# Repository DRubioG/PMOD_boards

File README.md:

# PMOD_boards
 This repository include all pmods created with KiCad

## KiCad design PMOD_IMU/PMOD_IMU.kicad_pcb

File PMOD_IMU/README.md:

# PMOD_boards
 This repository include all pmods created with KiCad

## Schematic

[schematic](/salida_esquematico.pdf)

## images

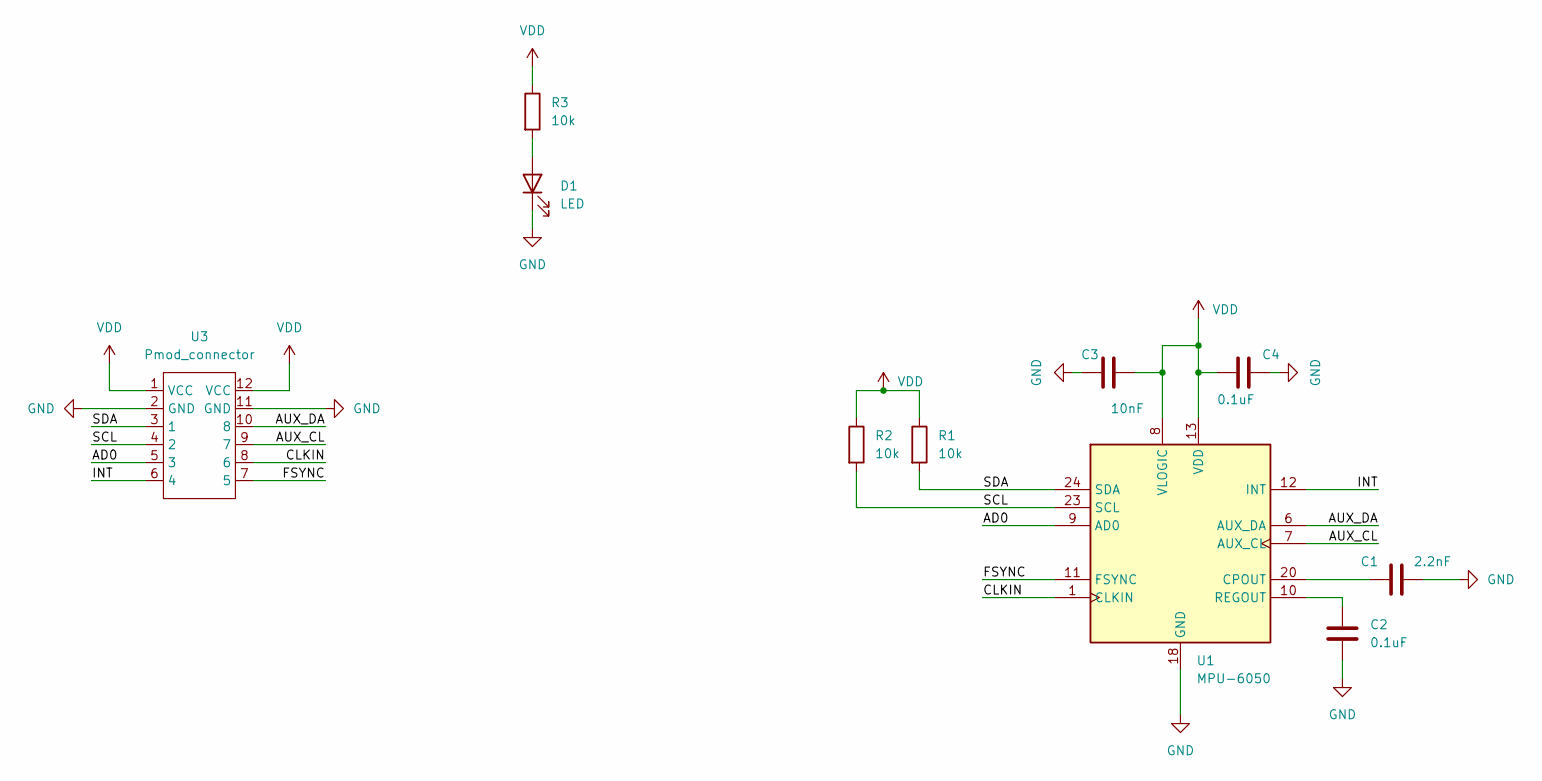
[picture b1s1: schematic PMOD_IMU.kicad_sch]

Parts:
C1: 2.2nF; C_0805_2012Metric_Pad1.18x1.45mm_HandSolder
C2, C4: 0.1uF; C_0805_2012Metric_Pad1.18x1.45mm_HandSolder
C3: 10nF; C_0805_2012Metric_Pad1.18x1.45mm_HandSolder
D1: LED; LED_0805_2012Metric_Pad1.15x1.40mm_HandSolder
R1, R2, R3: 10k; R_0805_2012Metric_Pad1.20x1.40mm_HandSolder
U1: MPU-6050; InvenSense_QFN-24_4x4mm_P0.5mm
U3: Pmod_connector; PMOD_EXTENSION_BOARD

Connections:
/AD0: U1.9 (AD0), U3.5 (3)
/AUX_CL: U1.7 (AUX_CL), U3.9 (7)
/AUX_DA: U1.6 (AUX_DA), U3.10 (8)
/CLKIN: U1.1 (CLKIN), U3.8 (6)
/FSYNC: U1.11 (FSYNC), U3.7 (5)
/INT: U1.12 (INT), U3.6 (4)
/SCL: R2.2, U1.23 (SCL), U3.4 (2)
/SDA: R1.2, U1.24 (SDA), U3.3 (1)
GND: C1.2, C2.1, C3.2, C4.2, D1.1 (K), U1.18 (GND), U3.2 (GND), U3.11 (GND)
unnamed: D1.2 (A), R3.2
unnamed: C1.1, U1.20 (CPOUT)
unnamed: C2.2, U1.10 (REGOUT)
VDD: C3.1, C4.1, R1.1, R2.1, R3.1, U1.8 (VLOGIC), U1.13 (VDD), U3.1 (VCC), U3.12 (VCC)

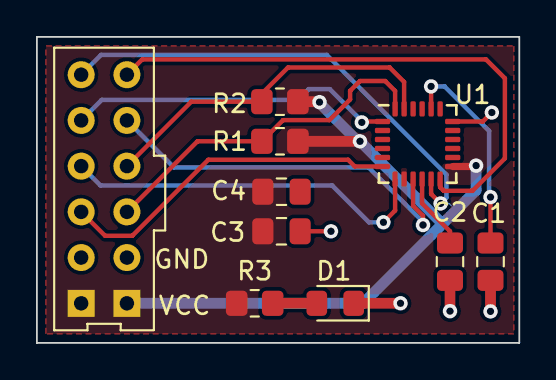
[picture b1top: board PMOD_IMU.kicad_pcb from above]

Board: 2 copper layers, 26.8 x 17.0 mm, 10 parts (0 on the bottom side), 13 nets.

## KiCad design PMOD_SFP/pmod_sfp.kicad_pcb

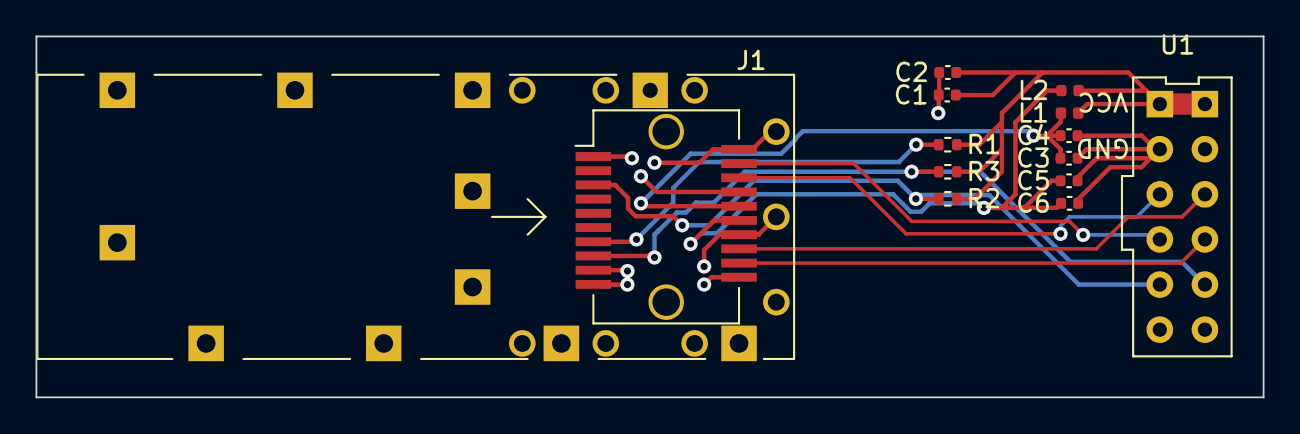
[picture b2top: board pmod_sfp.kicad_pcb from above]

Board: 2 copper layers, 69.1 x 20.3 mm, 13 parts (0 on the bottom side), 11 nets.

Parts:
C1: 22uF; C_0402_1005Metric
C2, C4, C6: 0.1uF; C_0402_1005Metric
C3, C5: 10uF; C_0402_1005Metric
J1: SFP; Connector_SFP_and_Cage
L1, L2: 220@100MHz; L_0402_1005Metric
R1, R2, R3: 4.7k; R_0402_1005Metric
U1: Pmod_connector; PMOD_EXTENSION_BOARD

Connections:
+3V3: C1.1, C2.1, L1.1, L2.1, R1.1, R2.1, R3.2, U1.1 (VCC), U1.12 (VCC)
/SFP_LOSS: J1.8 (RX_LOS), R3.1, U1.8 (6)
/SFP_RX_N: J1.12 (RD-), U1.9 (7)
/SFP_RX_P: J1.13 (RD+), U1.10 (8)
/SFP_TX_DIS: J1.3 (TX_DISABLE), R2.2, U1.5 (3)
/SFP_TX_N: J1.19 (TD-), U1.4 (2)
/SFP_TX_P: J1.18 (TD+), U1.3 (1)
GND: C1.2, C2.2, C3.2, C4.2, C5.2, C6.2, J1.1 (VeeT), J1.9 (VeeR), J1.10 (VeeR), J1.11 (VeeR), J1.14 (VeeR), J1.17 (VeeT), J1.20 (VeeT), J1.CAGE, U1.2 (GND), U1.11 (GND)
unnamed: C3.1, C4.1, J1.16 (VccT), L1.2
unnamed: C5.1, C6.1, J1.15 (VccR), L2.2
unnamed: J1.7 (RATE_SELECT), R1.2

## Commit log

2023-08-01 pruebas
